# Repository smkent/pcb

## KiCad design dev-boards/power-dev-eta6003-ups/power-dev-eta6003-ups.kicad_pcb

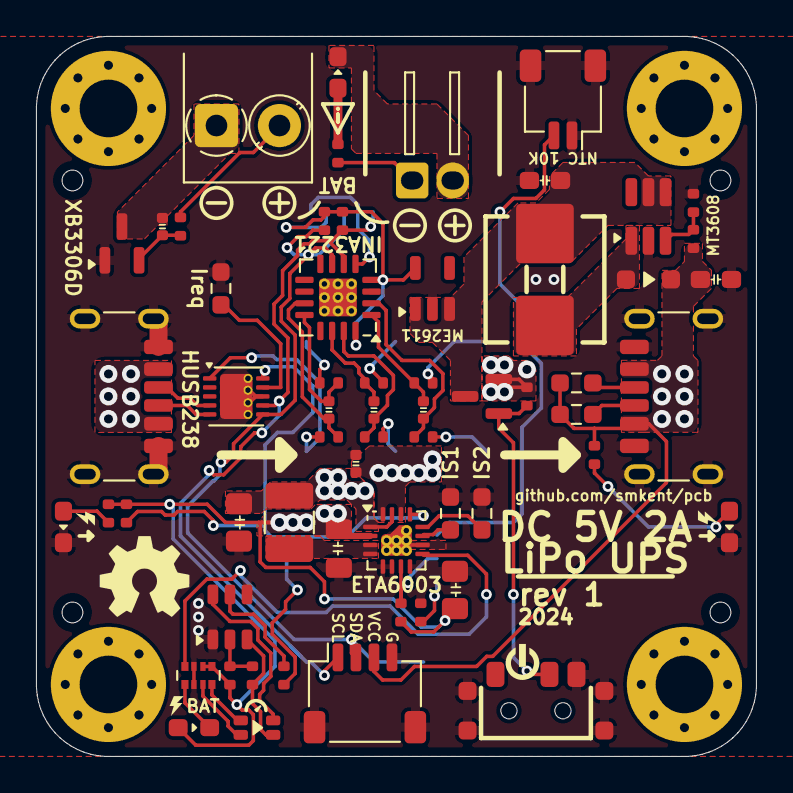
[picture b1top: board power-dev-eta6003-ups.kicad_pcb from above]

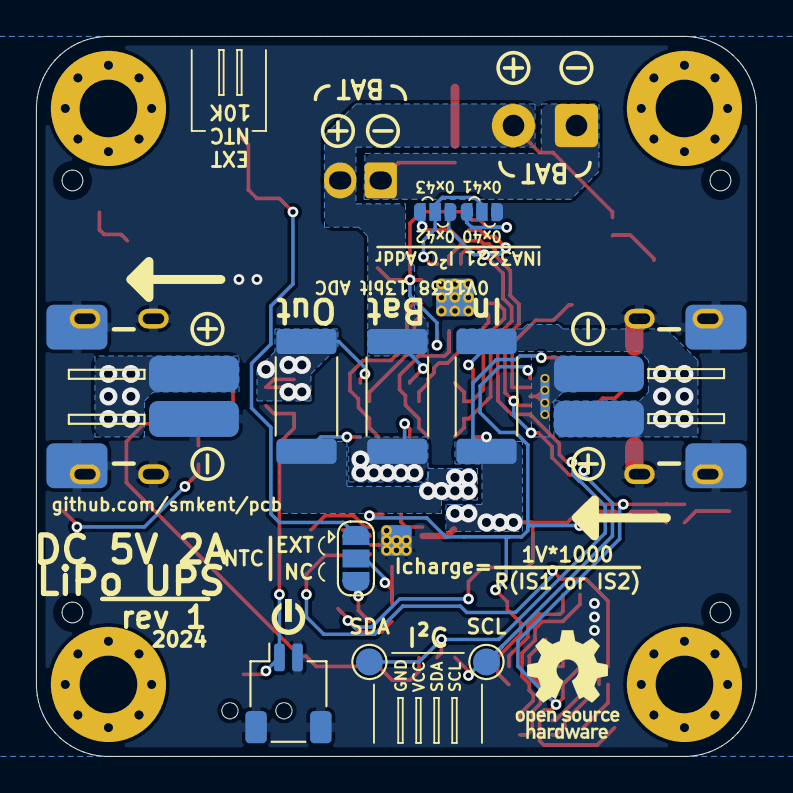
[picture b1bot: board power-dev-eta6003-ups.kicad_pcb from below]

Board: 2 copper layers, 40.0 x 40.0 mm, 71 parts (11 on the bottom side), 47 nets.

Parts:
C1: 22u; C_0805_2012Metric_Pad1.18x1.45mm_HandSolder
C2: 1u; C_0402_1005Metric_simple
C3: 10u; C_0805_2012Metric_Pad1.18x1.45mm_wide-center_HandSolder
C4, C7, C8, C9: 0u1; C_0402_1005Metric_simple
C5, C6: 10u; C_0603_1608Metric_Pad1.08x0.95mm_HandSolder
C10: 10u; C_0805_2012Metric_Pad1.18x1.45mm_HandSolder
D1: BAT60A; D_SOD-323_HandSoldering_simple
J1: P3.5; TerminalBlock_Phoenix_PT-1,5-2-3.5-H_1x02_P3.50mm_Horizonta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
J100, J200: USB_C_Receptacle_PowerOnly_6P; USB_C_Receptacle_GCT_USB4125-xx-x_6P_TopMnt_Horizontal_hand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
J101, J201: JST XH/PH; Conn_Combo_JST-1x02-XH_PH-SMD-alt-pad2gnd
J300: JST XH/PH; Conn_Combo_JST-1x02-XH_PH-THT-pad2gnd
J301, J500: JST SH; JST_SH_SM02B-SRSS-TB_1x02-1MP_P1.00mm_Horizontal
J400: JST SH; JST_SH_SM04B-SRSS-TB_1x04-1MP_P1.00mm_Horizontal
JP1: NTC; SolderJumper-3_P1.3mm_Open_RoundedPad1.0x1.5mm
JP2, JP3: VS/GND; SolderJumper-3_P1.0mm_Open_RoundedPad_simple
L1: 2u2; L_1210_3225Metric_Pad1.42x2.65mm_HandSolder
L2: 4u7; Inductor_Multi_7.0x6.6_1210
LED1: Pink; LED_0603_1608Metric_Pad1.05x0.95mm_HandSolder_simple
LED2: LED; LED-ARRAY-SMD_4P-L2.0-W1.3-RD
LED3: White; LED_0603_1608Metric_Pad1.05x0.95mm_HandSolder_simple
LED4: Red; LED_0603_1608Metric_Pad1.05x0.95mm_HandSolder_simple
LED5: Blue; LED_0603_1608Metric_Pad1.05x0.95mm_HandSolder_simple
Q1: 2N7002DW; SOT-23-6_trimmed-pads_simple
Q2: AO3401A; SOT-23_simple
R1, R2, R8, R9, R10, R13, R25, R104: 10K; R_0402_1005Metric_simple
R3, R11, R103: 5K1; R_0402_1005Metric_simple
R4: 2K; R_0603_1608Metric_Pad0.98x0.95mm_HandSolder
R5: 1K; R_0603_1608Metric_Pad0.98x0.95mm_HandSolder
R6, R7, R27, R28, R29, R30, R31, R32: 10R; R_0402_1005Metric_simple
R12: 100R; R_0402_1005Metric_simple
R24: 75K; R_0402_1005Metric_simple
R102, R201, R202: 22K; R_0603_1608Metric_Pad0.98x0.95mm_HandSolder
RN1: 5K1; R_Array_Convex_4x0402
SR1, SR2, SR3: R040; R_2512_6332Metric_Pad1.40x3.35mm_HandSolder
SW1: SW_SPDT; SW-SMD_3P-P1.50_L2.7-W6.6
TP1, TP2: TestPoint_Pad_D1.5mm
U1: ETA6003; ETA6003_QFN-16-1EP_3x3mm_P0.5mm_EP1.7x1.7mm_ThermalVias
U2: XB3306D; SOT-23_simple
U3: ME6211C33M5; SOT-23-5_simple
U4: INA3221; Texas_RGV0016A_VQFN-16-1EP_4x4mm_P0.65mm_EP2.1x2.1mm_Therma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
U5: MT3608; SOT-23-6_Handsoldering_simple
U101: HUSB238_002DD; WDFN-10-1EP_3x3mm_P0.5mm_EP1.8x2.5mm_ThermalVias_half

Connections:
+3V3: JP2.1 (A), R8.1, R9.1, U3.5 (V_{OUT}), U4.4 (VS), U4.16 (VPU)
B+: J1.1, J300.1, LED4.1 (K), R12.2, R30.2, SR2.1
B-: C4.2, J1.2, J300.2, R11.2, U2.3 (GND)
BAT_SHUNT: C2.1, R29.2, SR2.2, U1.14 (BATT), U1.16 (BATT)
BOOST_SW: D1.2 (A), L2.2, U5.1 (SW)
EXT_POWER_SWITCH: J500.1, Q2.1 (G), R10.2, SW1.2 (B)
FB: R24.2, R25.1, U5.3 (FB)
GND: C1.2, C2.2, C3.1, C5.2, C6.2, C10.1, J100.A12 (GND), J100.B12 (GND), J100.S1 (SHIELD), J101.2, J101.MP (MountPin), J200.A12 (GND), J200.B12 (GND), J200.S1 (SHIELD), J201.2, J201.MP (MountPin), J301.1, J301.MP (MountPin), J400.4, J400.MP (MountPin), J500.2, J500.MP (MountPin), JP2.3 (B), LED3.1 (K), LED5.1 (K), Q1.1 (S), Q1.4 (S), R2.1, R4.2, R5.2, R25.2, R102.2, RN1.2 (R2.1), RN1.7 (R2.2), SW1.3 (C), SW1.MP (MountPin), U1.5 (PGND), U1.6 (ENB), U1.8 (ENPPB), U1.10 (GND), U1.17 (EP), U2.1 (VM), U3.2 (V_{SS}), U4.3 (GND), U5.2 (GND), U101.8 (VSET), U101.11 (GND)
LOAD_SHUNT: C1.1, L1.1, R31.2, SR3.2, U1.1 (SYS), U1.15 (SYS)
LOAD_SHUNT_OUT: Q2.2 (S), R10.1, R32.2, SR3.1
NTC: JP1.2 (C), R1.1, U1.7 (NTC)
NTC_CONN: J301.2, JP1.1 (A)
unnamed: J100.A5 (CC1), U101.4 (CC1)
unnamed: J100.B5 (CC2), U101.5 (CC2)
unnamed: J200.A5 (CC1), R201.2
unnamed: J200.B5 (CC2), R202.2
unnamed: JP1.3 (B), R2.2
unnamed: JP2.2 (C), JP3.2 (C), U4.5 (A0)
unnamed: LED1.1 (K), RN1.1 (R1.1)
unnamed: LED2.1 (RED_A), RN1.3 (R3.1)
unnamed: LED2.2 (RED_K), Q1.3 (D), R7.1
unnamed: LED2.3 (BLUE_A), RN1.4 (R4.1)
unnamed: LED2.4 (BLUE_K), Q1.6 (D)
unnamed: LED3.2 (A), R103.2
unnamed: LED4.2 (A), R11.1
unnamed: LED5.2 (A), R3.2
unnamed: Q1.5 (G), R6.1
unnamed: Q1.2 (G), R7.2, R13.2
unnamed: RN1.8 (R1.2), U1.9 (STAT)
unnamed: R4.1, U1.11 (ISET1)
unnamed: R5.1, U1.12 (ISET2)
unnamed: C4.1, R12.1, U2.2 (VDD)
unnamed: C7.1, R27.2, U4.12 (IN+1)
unnamed: C8.1, R29.1, U4.15 (IN+2)
unnamed: C9.1, R31.1, U4.2 (IN+3)
unnamed: C7.2, R28.2, U4.11 (IN-1)
unnamed: C8.2, R30.1, U4.14 (IN-2)
unnamed: C9.2, R32.1, U4.1 (IN-3)
unnamed: R102.1, U101.9 (ISET)
SCL: J400.1, JP3.1 (A), R9.2, TP1.1, U4.6 (SCL), U101.7 (SCL)
SDA: J400.2, JP3.3 (B), R8.2, TP2.1, U4.7 (SDA), U101.6 (SDA)
SW: L1.2, U1.3 (SW), U1.4 (SW)
USB_DET: R6.2, R104.2, U1.13 (USB_DET), U101.10 (GATE)
VIN: J100.A9 (VBUS), J100.B9 (VBUS), J101.1, R27.1, SR1.1
VIN_SHUNT: C3.2, C10.2, LED1.2 (A), R1.2, R13.1, R28.1, R103.1, R104.1, RN1.5 (R4.2), RN1.6 (R3.2), SR1.2, U1.2 (IN), U101.1 (VIN)
VOUT: C6.1, D1.1 (K), J200.A9 (VBUS), J200.B9 (VBUS), J201.1, J400.3, R3.1, R24.1, R201.1, R202.1
VSYS: C5.1, L2.1, Q2.3 (D), U3.1 (V_{IN}), U3.3 (CE), U5.4 (EN), U5.5 (IN)

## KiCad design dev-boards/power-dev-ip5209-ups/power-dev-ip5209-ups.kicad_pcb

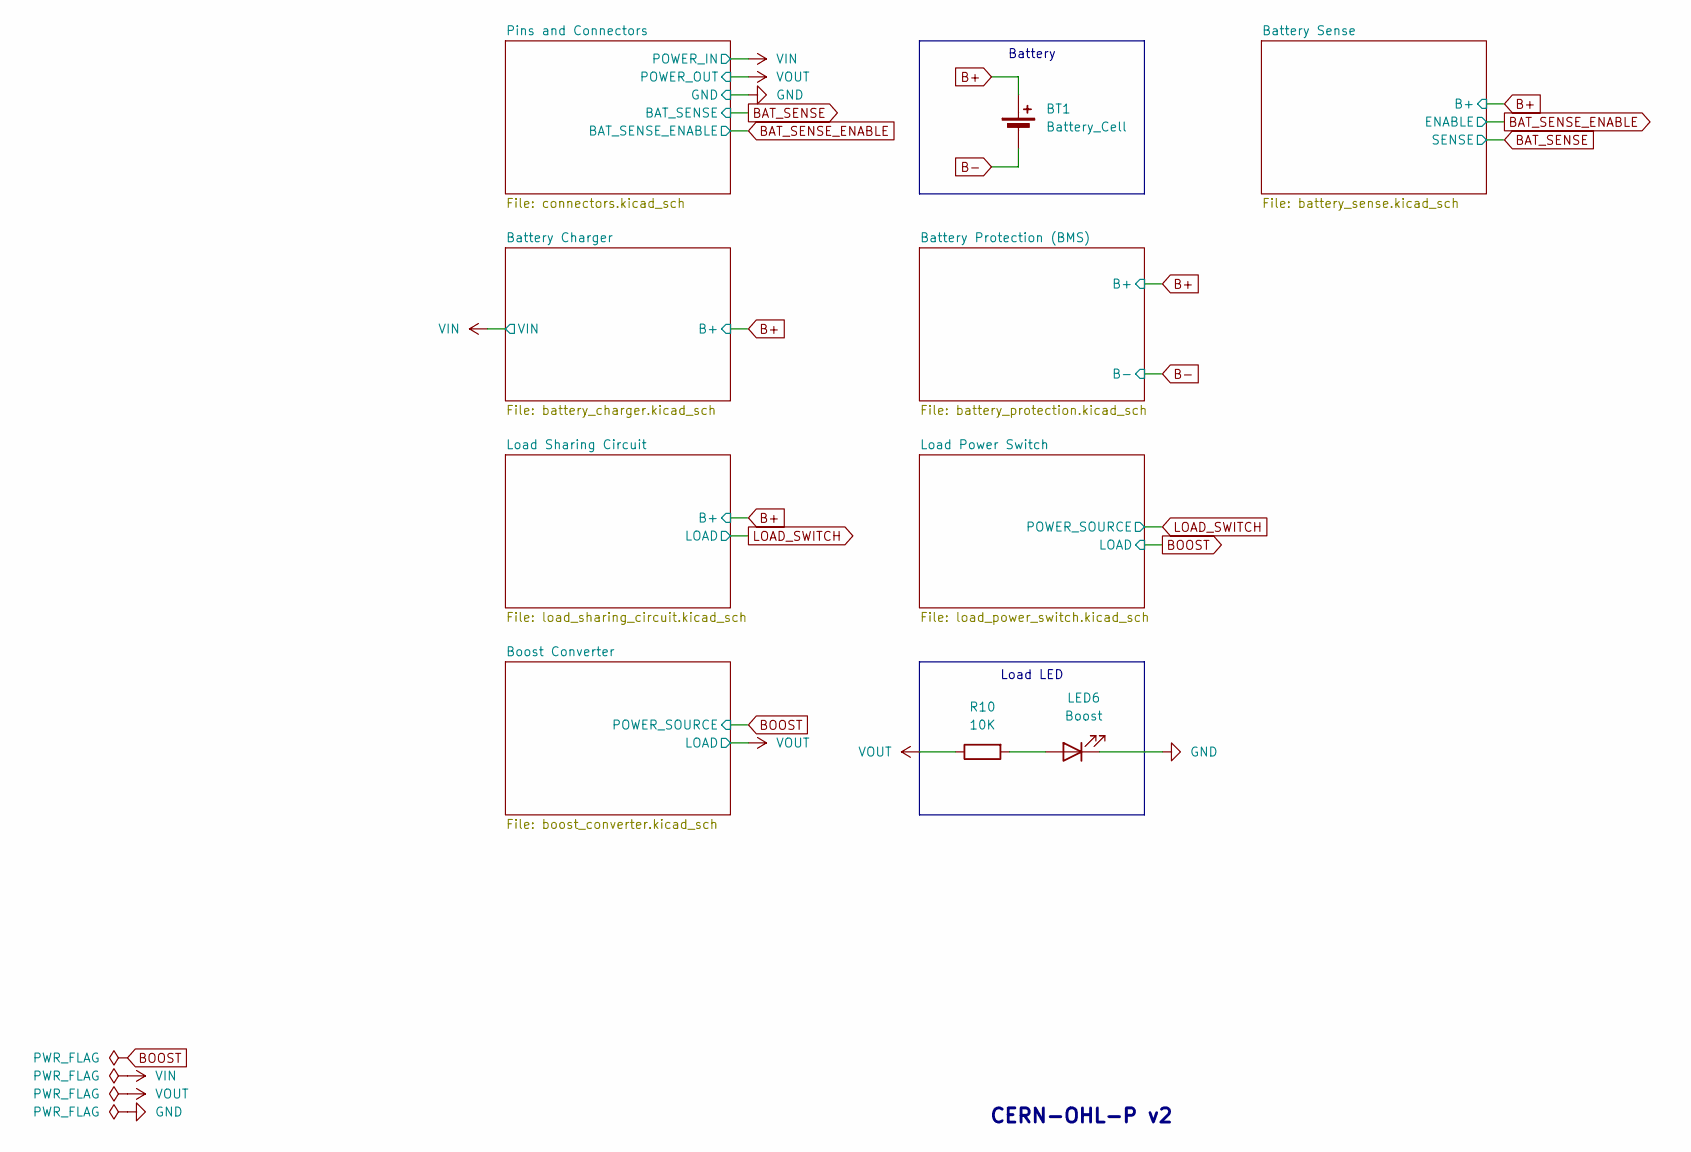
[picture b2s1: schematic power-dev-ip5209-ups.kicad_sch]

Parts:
BT1: Battery_Cell; JST_XH_S2B-XH-2AW_1x02_P2.50mm_pad2gnd_trim
LED6: Boost; LED_0805_2012Metric_Pad1.15x1.40mm_HandSolder_simple
R10: 10K; R_0402_1005Metric; LCSC Part C25744

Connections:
B+: BT1.1 (+); also elsewhere on the board
B-: BT1.2 (-); also elsewhere on the board
GND: LED6.1 (K); also elsewhere on the board
unnamed: LED6.2 (A), R10.2
VOUT: R10.1; also elsewhere on the board

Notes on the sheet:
Battery
Load LED
CERN-OHL-P v2

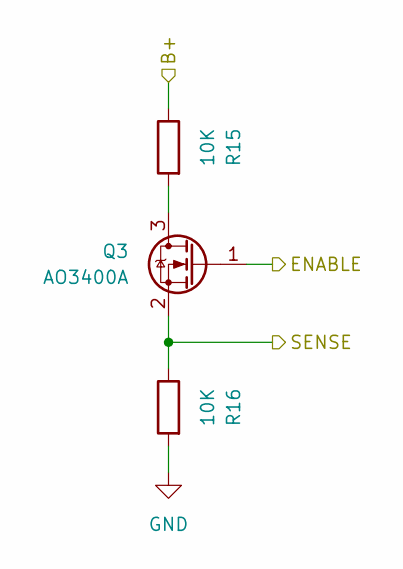
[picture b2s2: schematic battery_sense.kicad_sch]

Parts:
Q3: AO3400A; SOT-23
R15, R16: 10K; R_0402_1005Metric; LCSC Part C25744

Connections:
B+: R15.1; also elsewhere on the board
BAT_SENSE: Q3.2 (S), R16.1; also elsewhere on the board
BAT_SENSE_ENABLE: Q3.1 (G); also elsewhere on the board
GND: R16.2; also elsewhere on the board
unnamed: Q3.3 (D), R15.2

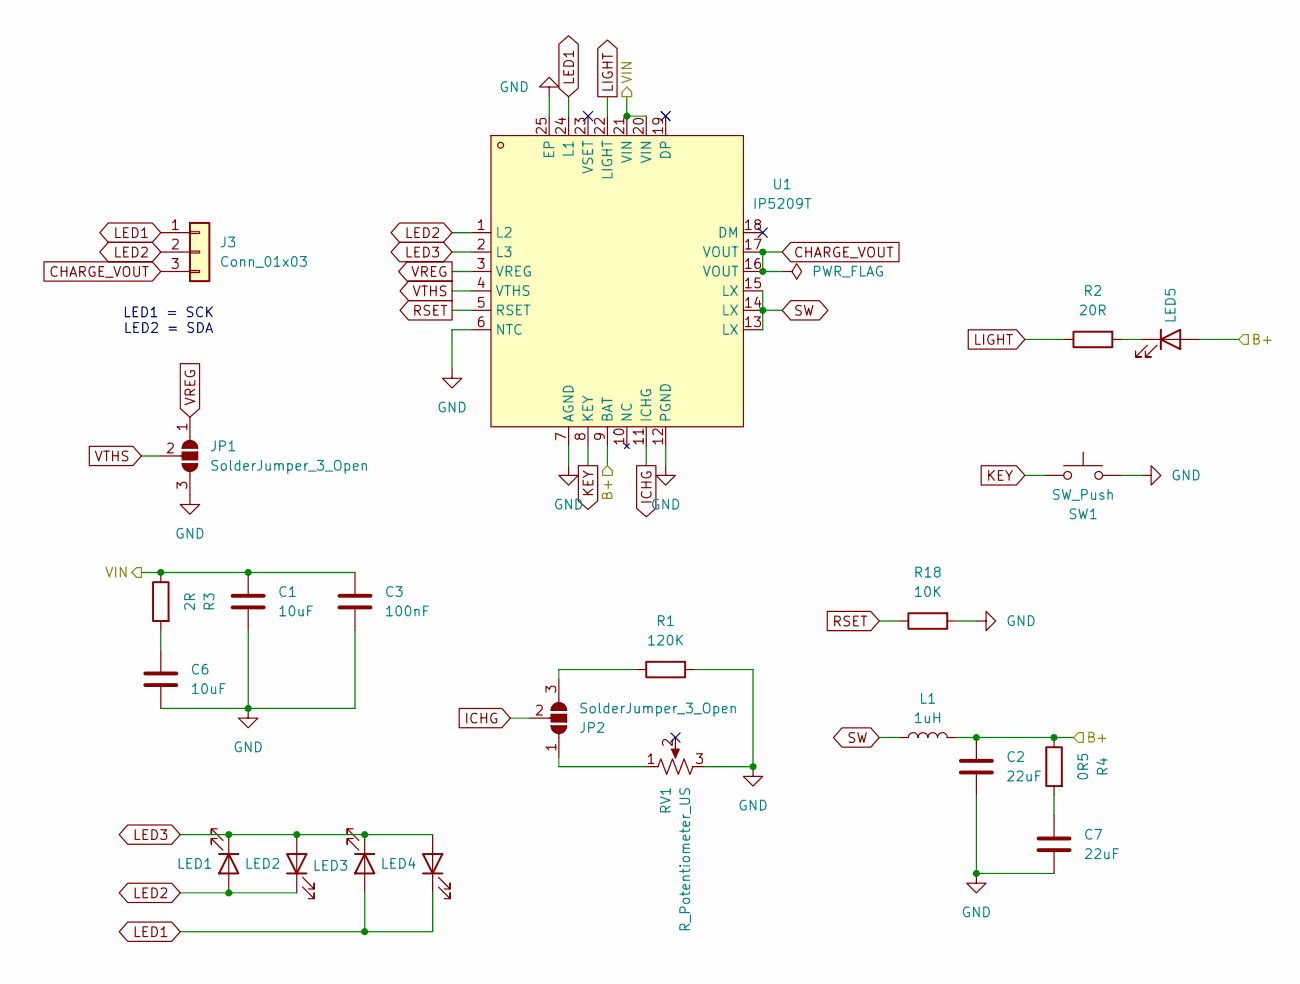
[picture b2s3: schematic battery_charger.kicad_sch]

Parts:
C1, C6: 10uF; C_0402_1005Metric; LCSC Part C15525
C2, C7: 22uF; C_0603_1608Metric; LCSC Part C59461
C3: 100nF; C_0402_1005Metric; LCSC Part C307331
J3: Conn_01x03; PinHeader_1x03_P2.54mm_Vertical_simple
JP1, JP2: SolderJumper_3_Open; SolderJumper-3_P1.3mm_Open_RoundedPad1.0x1.5mm
L1: 1uH; L_1210_3225Metric; LCSC Part C3002559
LED1, LED2, LED3, LED4: LED_0805_2012Metric_Pad1.15x1.40mm_HandSolder_simple
LED5: LED-SMD_3P-L5.7-W3.0-RD
R1: 120K; R_0805_2012Metric_Pad1.20x1.40mm_HandSolder; LCSC Part C17436
R2: 20R; R_0805_2012Metric_Pad1.20x1.40mm_HandSolder; LCSC Part C17544
R3: 2R; R_0603_1608Metric; LCSC Part C22977
R4: 0R5; R_0805_2012Metric_Pad1.20x1.40mm_HandSolder
R18: 10K; R_0805_2012Metric_Pad1.20x1.40mm_HandSolder
RV1: R_Potentiometer_US; RES-ADJ-SMD_VG039NCH
SW1: SW_Push; SW-SMD_BZCN_TSA002A35XXX
U1: IP5209T; QFN-24-1EP_4x4mm_P0.5mm_EP2.6x2.6mm_ThermalVias; LCSC Part C284964

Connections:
B+: C2.1, L1.2, LED5.2 (A), R4.1, U1.9 (BAT); also elsewhere on the board
CHARGE_VOUT: J3.3, U1.16 (VOUT), U1.17 (VOUT)
GND: C1.2, C2.2, C3.2, C6.2, C7.2, JP1.3 (B), R1.2, R18.2, RV1.3, SW1.1, U1.6 (NTC), U1.7 (AGND), U1.12 (PGND), U1.25 (EP); also elsewhere on the board
ICHG: JP2.2 (C), U1.11 (ICHG)
KEY: SW1.2, U1.8 (KEY)
LED1: J3.1, LED3.2 (A), LED4.1 (K), U1.24 (L1)
LED2: J3.2, LED1.2 (A), LED2.1 (K), U1.1 (L2)
LED3: LED1.1 (K), LED2.2 (A), LED3.1 (K), LED4.2 (A), U1.2 (L3)
LIGHT: R2.1, U1.22 (LIGHT)
unnamed: C6.1, R3.2
unnamed: C7.1, R4.2
unnamed: JP2.1 (A), RV1.1
unnamed: JP2.3 (B), R1.1
unnamed: LED5.1 (K), R2.2
RSET: R18.1, U1.5 (RSET)
SW: L1.1, U1.13 (LX), U1.14 (LX), U1.15 (LX)
VIN: C1.1, C3.1, R3.1, U1.20 (VIN), U1.21 (VIN); also elsewhere on the board
VREG: JP1.1 (A), U1.3 (VREG)
VTHS: JP1.2 (C), U1.4 (VTHS)

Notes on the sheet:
LED1 = SCK LED2 = SDA

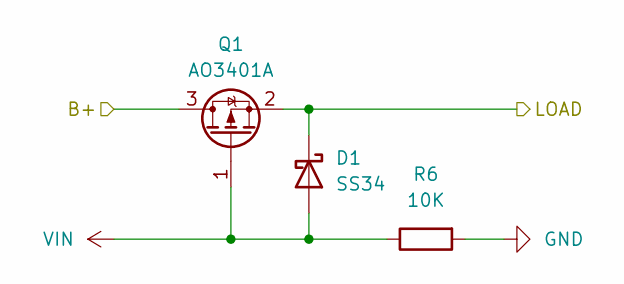
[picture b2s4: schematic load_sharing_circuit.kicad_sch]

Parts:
D1: SS34; D_SMA_simple; LCSC Part C8678
Q1: AO3401A; SOT-23; LCSC Part C15127
R6: 10K; R_0402_1005Metric; LCSC Part C25744

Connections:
B+: Q1.3 (D); also elsewhere on the board
GND: R6.2; also elsewhere on the board
LOAD_SWITCH: D1.1 (K), Q1.2 (S); also elsewhere on the board
VIN: D1.2 (A), Q1.1 (G), R6.1; also elsewhere on the board

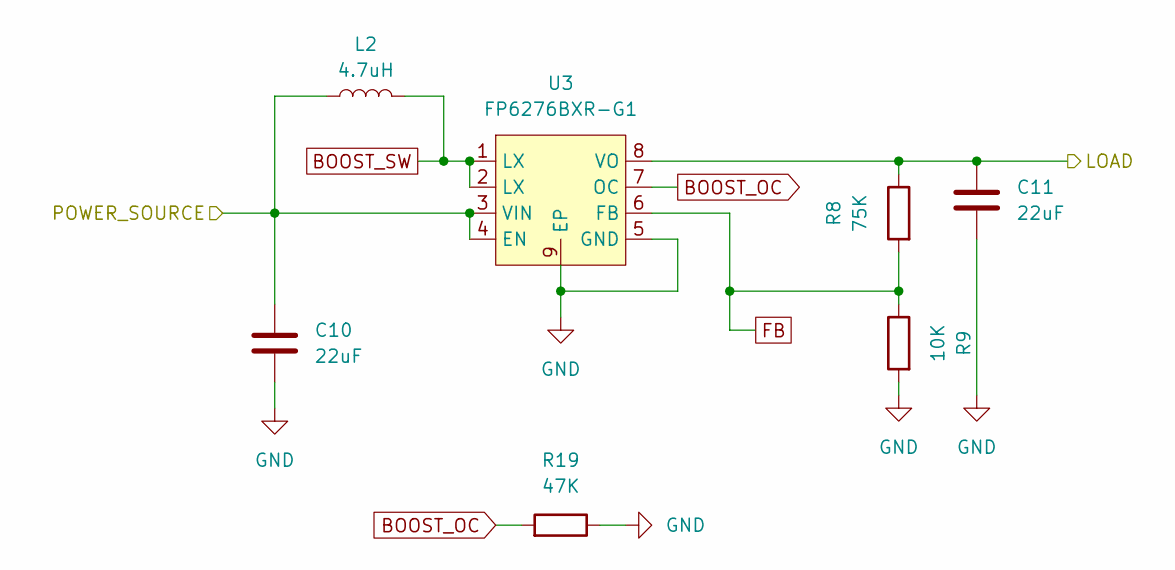
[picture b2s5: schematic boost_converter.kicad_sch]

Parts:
C10, C11: 22uF; C_0603_1608Metric; LCSC Part C59461
L2: 4.7uH; IND-SMD_L7.0-W6.6; LCSC Part C5307631
R8: 75K; R_0402_1005Metric; LCSC Part C25798
R9: 10K; R_0402_1005Metric; LCSC Part C25744
R19: 47K; R_0805_2012Metric_Pad1.20x1.40mm_HandSolder; LCSC Part C17713
U3: FP6276BXR-G1; SOIC-8-1EP_3.9x4.9mm_P1.27mm_EP2.41x3.3mm_ThermalVias_Custo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; LCSC Part C82652

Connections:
BOOST: C10.1, L2.1, U3.3 (VIN), U3.4 (EN); also elsewhere on the board
BOOST_OC: R19.2, U3.7 (OC)
BOOST_SW: L2.2, U3.1 (LX), U3.2 (LX)
FB: R8.2, R9.1, U3.6 (FB)
GND: C10.2, C11.2, R9.2, R19.1, U3.5 (GND), U3.9 (EP); also elsewhere on the board
VOUT: C11.1, R8.1, U3.8 (VO); also elsewhere on the board

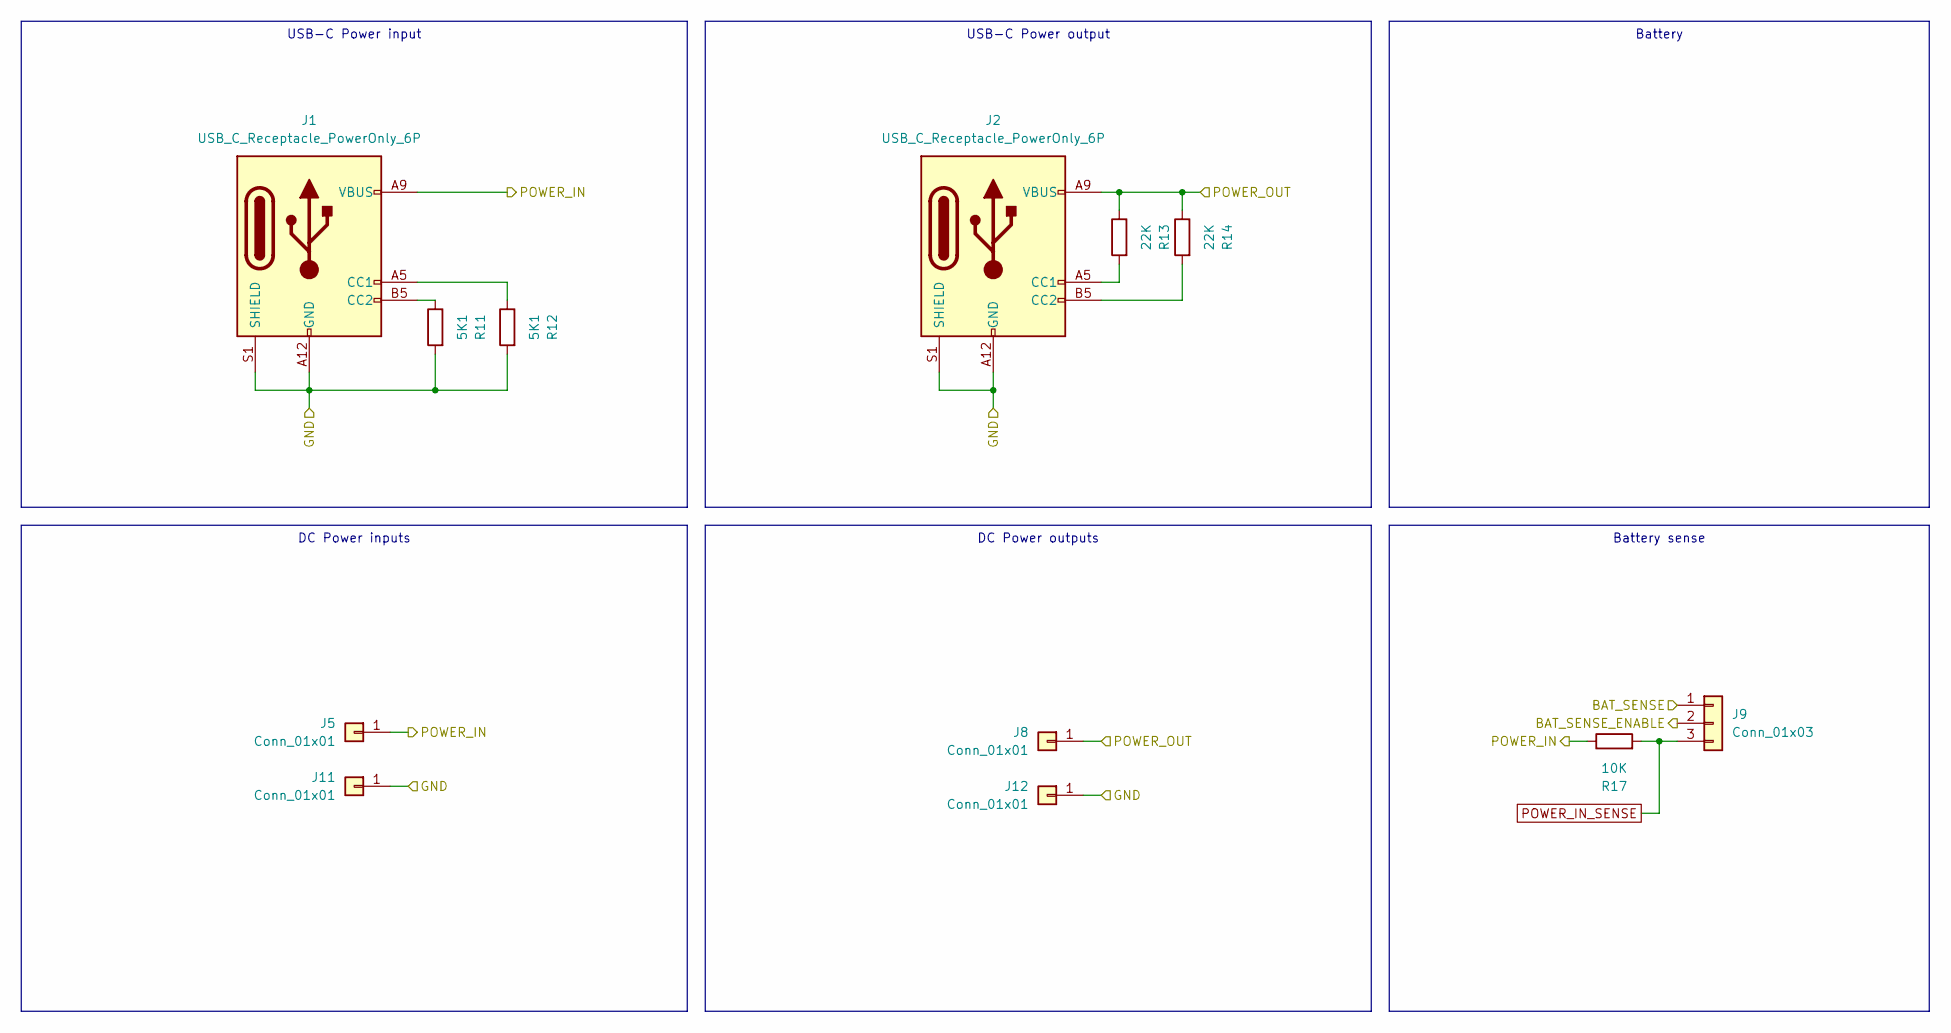
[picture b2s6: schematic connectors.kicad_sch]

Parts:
J1, J2: USB_C_Receptacle_PowerOnly_6P; USB_C_Receptacle_GCT_USB4125-xx-x_6P_TopMnt_Horizontal_hand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
J5, J8: Conn_01x01; PinHeader_1x01_P2.54mm_simple
J9: Conn_01x03; PinHeader_1x03_P2.54mm_Vertical_simple
J11, J12: Conn_01x01; PinHeader_1x01_P2.54mm_simple_square
R11, R12: 5K1; R_0402_1005Metric; LCSC Part C25905
R13, R14: 22K; R_0402_1005Metric; LCSC Part C25768
R17: 10K; R_0402_1005Metric; LCSC Part C25744

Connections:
BAT_SENSE: J9.1; also elsewhere on the board
BAT_SENSE_ENABLE: J9.2; also elsewhere on the board
GND: J1.A12 (GND), J1.B12 (GND), J1.S1 (SHIELD), J2.A12 (GND), J2.B12 (GND), J2.S1 (SHIELD), J11.1, J12.1, R11.2, R12.2; also elsewhere on the board
unnamed: J1.A5 (CC1), R12.1
unnamed: J1.B5 (CC2), R11.1
unnamed: J2.A5 (CC1), R13.2
unnamed: J2.B5 (CC2), R14.2
POWER_IN_SENSE: J9.3, R17.2
VIN: J1.A9 (VBUS), J1.B9 (VBUS), J5.1, R17.1; also elsewhere on the board
VOUT: J2.A9 (VBUS), J2.B9 (VBUS), J8.1, R13.1, R14.1; also elsewhere on the board

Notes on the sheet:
DC Power outputs
USB-C Power output
DC Power inputs
Battery sense
USB-C Power input
Battery

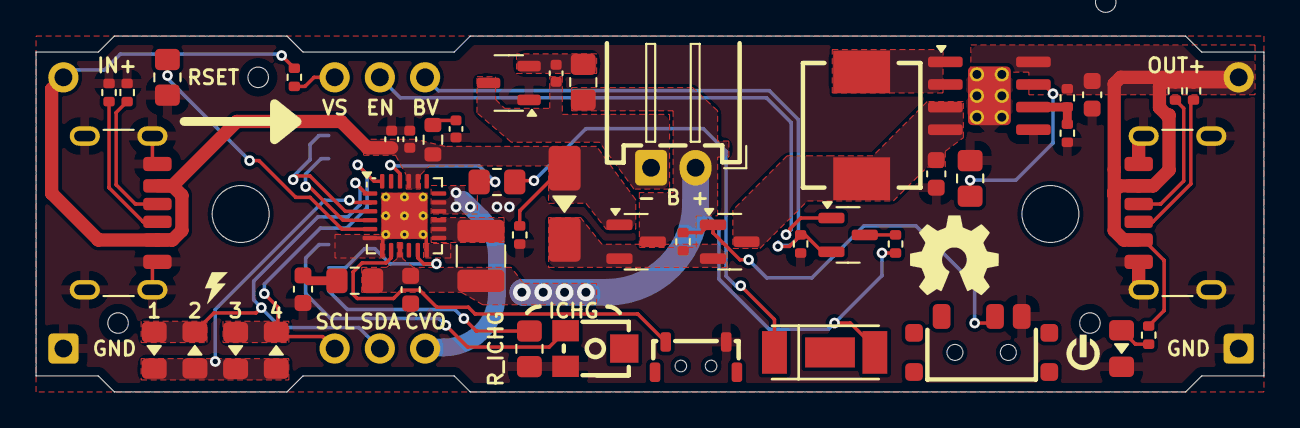
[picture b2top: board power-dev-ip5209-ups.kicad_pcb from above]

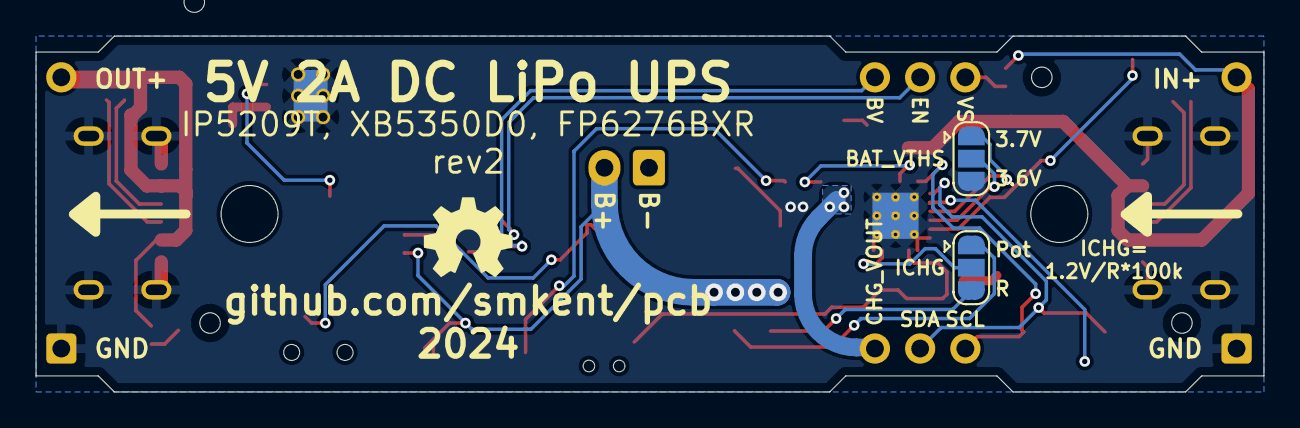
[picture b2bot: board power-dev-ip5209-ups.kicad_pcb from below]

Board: 2 copper layers, 69.0 x 20.0 mm, 56 parts (8 on the bottom side), 37 nets.

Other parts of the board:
C9: 0.1uF; C_0402_1005Metric
Q2: AO3401A; SOT-23
R5: 100R; R_0805_2012Metric_Pad1.20x1.40mm_HandSolder
R7: 10K; R_0402_1005Metric
SW2: SW_SPDT; SW-SMD_3P-P1.50_L2.7-W6.6
U2: XB3306D; SOT-23-3

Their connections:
B+: R5.1; also elsewhere on the board
B-: C9.1, U2.3 (GND); also elsewhere on the board
BATVDD: C9.2, R5.2, U2.2 (VDD)
BOOST: Q2.3 (D); also elsewhere on the board
GND: SW2.3 (C), U2.1 (VM); also elsewhere on the board
LOAD_SWITCH: Q2.2 (S), R7.1; also elsewhere on the board
unnamed: Q2.1 (G), R7.2, SW2.2 (B)

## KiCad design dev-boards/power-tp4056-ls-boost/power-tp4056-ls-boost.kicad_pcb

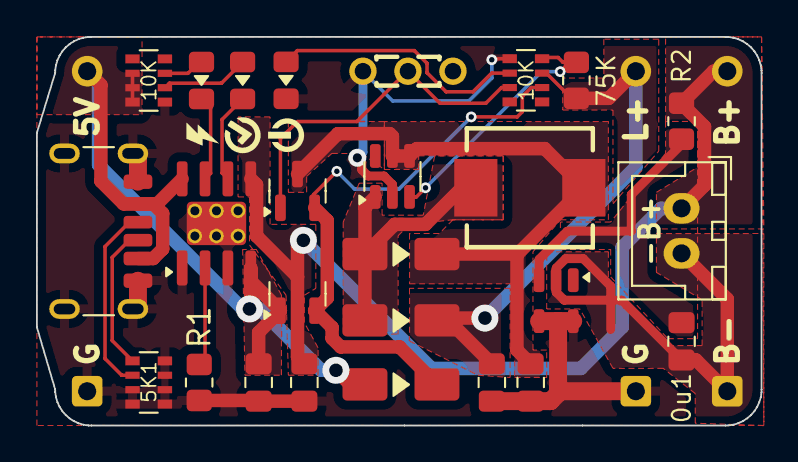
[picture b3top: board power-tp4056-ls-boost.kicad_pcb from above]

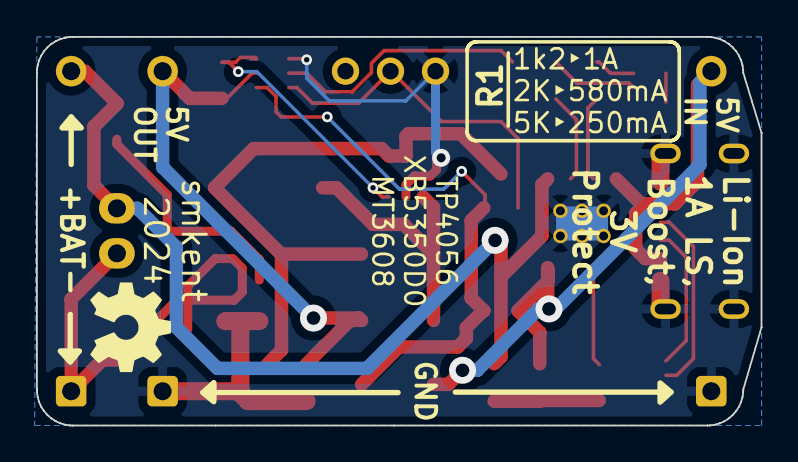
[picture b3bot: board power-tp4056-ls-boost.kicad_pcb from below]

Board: 2 copper layers, 40.3 x 21.6 mm, 32 parts (6 on the bottom side), 19 nets.

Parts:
BT1: Battery_Cell; JST_XH_B2B-XH-A_1x02_P2.50mm_Vertical_simple
C1, C2, C4, C5: 10uF; C_0805_2012Metric_Pad1.18x1.45mm_HandSolder
C3: 0.1uF; C_0805_2012Metric_Pad1.18x1.45mm_HandSolder
D1, D2, D3: SS34; D_SMA_simple
J0: USB_C_Receptacle_PowerOnly_6P; USB_C_Receptacle_GCT_USB4125-xx-x_6P_TopMnt_Horizontal_hand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
J1, J3, J5: Conn_01x01; PinHeader_1x01_P2.54mm_simple
J2, J4, J6: Conn_01x01; PinHeader_1x01_P2.54mm_simple_square
L1: 22uH; IND-SMD_L7.0-W6.6
LED1: Charge; LED_0805_2012Metric_Pad1.15x1.40mm_HandSolder_simple
LED2: Done; LED_0805_2012Metric_Pad1.15x1.40mm_HandSolder_simple
LED3: Boost; LED_0805_2012Metric_Pad1.15x1.40mm_HandSolder_simple
Q1, Q2: AO3401A; SOT-23
R1: 1K2; R_0805_2012Metric_Pad1.20x1.40mm_HandSolder
R2: 100R; R_0805_2012Metric_Pad1.20x1.40mm_HandSolder
R3: 75K; R_0805_2012Metric_Pad1.20x1.40mm_HandSolder
RN1, RN3: 10K; R_Array_Convex_4x0603
RN2: 5K1; R_Array_Convex_4x0603
SW1: SW_SPDT; SW-TH_DEALON_SS-12D01-GX_simple
U1: TP4056; SOIC-8-1EP_3.9x4.9mm_P1.27mm_EP2.41x3.3mm_ThermalVias_Custo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
U2: XB5350D0; SOT-23-5_simple
U3: MT3608; SOT-23-6

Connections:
B+: BT1.1 (+), C2.2, J3.1, Q1.3 (D), R2.1, U1.5 (BAT)
B-: BT1.2 (-), C3.1, J4.1, U2.2 (GND)
BATVDD: C3.2, R2.2, U2.3 (VDD)
BOOST: C4.1, D3.1 (K), L1.1, Q2.3 (D), U3.4 (EN), U3.5 (IN)
GND: C1.2, C2.1, C4.2, C5.2, J0.A12 (GND), J0.B12 (GND), J0.S1 (SHIELD), J2.1, J6.1, LED3.1 (K), R1.2, RN1.1 (R1.1), RN2.3 (R3.1), RN2.4 (R4.1), RN2.5 (R4.2), RN2.6 (R3.2), RN2.7 (R2.2), RN2.8 (R1.2), RN3.5 (R4.2), SW1.3 (C), U1.1 (TEMP), U1.3 (GND), U1.9 (EP), U2.4 (VM), U2.5 (VM), U3.2 (GND)
LOAD_SWITCH: D1.1 (K), Q1.2 (S), Q2.2 (S), RN3.2 (R2.1)
unnamed: D2.2 (A), D3.2 (A), L1.2, U3.1 (SW)
unnamed: J0.A5 (CC1), RN2.2 (R2.1)
unnamed: J0.B5 (CC2), RN2.1 (R1.1)
unnamed: LED1.2 (A), RN1.3 (R3.1)
unnamed: LED1.1 (K), U1.7 (~CHRG)
unnamed: LED2.2 (A), RN1.2 (R2.1)
unnamed: LED2.1 (K), U1.6 (~STDBY)
unnamed: LED3.2 (A), RN3.6 (R3.2)
unnamed: Q2.1 (G), RN3.7 (R2.2), SW1.2 (B)
unnamed: R3.2, RN3.4 (R4.1), U3.3 (FB)
unnamed: R1.1, U1.2 (PROG)
VIN: C1.1, D1.2 (A), J0.A9 (VBUS), J0.B9 (VBUS), J1.1, Q1.1 (G), RN1.6 (R3.2), RN1.7 (R2.2), RN1.8 (R1.2), U1.4 (VCC), U1.8 (CE)
VOUT: C5.1, D2.1 (K), J5.1, R3.1, RN3.3 (R3.1)

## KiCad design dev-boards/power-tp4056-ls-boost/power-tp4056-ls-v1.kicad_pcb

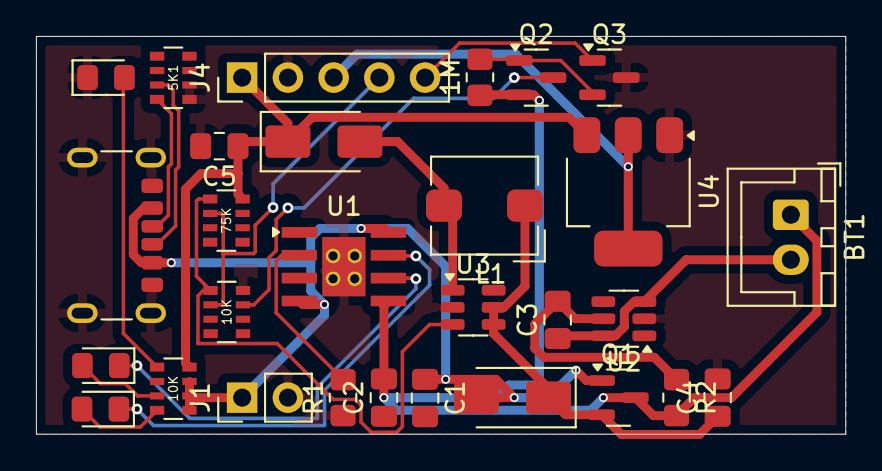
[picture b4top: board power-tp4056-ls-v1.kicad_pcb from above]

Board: 2 copper layers, 45.0 x 22.1 mm, 29 parts (0 on the bottom side), 22 nets.

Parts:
BT1: Battery_Cell; JST_XH_B2B-XH-A_1x02_P2.50mm_Vertical
C1, C2, C4, C5: 10uF; C_0805_2012Metric_Pad1.18x1.45mm_HandSolder
C3: 0.1uF; C_0805_2012Metric_Pad1.18x1.45mm_HandSolder
D1, D3: SS34; D_SMA
J1: Conn_01x02; PinHeader_1x02_P2.54mm_Vertical
J4: Conn_01x05; PinHeader_1x05_P2.54mm_Vertical
J5: USB_C_Receptacle_PowerOnly_6P; USB_C_Receptacle_GCT_USB4125-xx-x_6P_TopMnt_Horizontal
L1: 22uH; L_Bourns_SRP5030T
LED1: Charge; LED_0805_2012Metric_Pad1.15x1.40mm_HandSolder
LED2: Done; LED_0805_2012Metric_Pad1.15x1.40mm_HandSolder
LED3: Boost; LED_0805_2012Metric_Pad1.15x1.40mm_HandSolder
Q1, Q2: AO3401A; SOT-23
Q3: BSS138; SOT-23
R1: 1K2; R_0805_2012Metric_Pad1.20x1.40mm_HandSolder
R2: 100R; R_0805_2012Metric_Pad1.20x1.40mm_HandSolder
R5: 1M; R_0805_2012Metric_Pad1.20x1.40mm_HandSolder
RN1, RN3: 10K; R_Array_Convex_4x0603
RN2: 5K1; R_Array_Convex_4x0603
RN4: 75K; R_Array_Convex_4x0603
U1: TP4056; TP4056-SOP-8-EP-Vias
U2: XB5307H; SOT-23-6
U3: MT3608; SOT-23-6
U4: AMS1117-3.3; SOT-223-3_TabPin2

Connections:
+3V3: J4.3, U4.2 (VO)
B+: BT1.1 (+), C2.2, Q1.3 (D), Q2.2 (S), R2.2, R5.2, U1.5 (BAT)
B-: BT1.2 (-), C3.1, U2.3 (GND), U2.6 (GND)
BAT_SENSE: J4.4, RN3.2 (R2.1), RN4.2 (R2.1)
BAT_SENSE_SWITCH: J4.5, Q3.1 (G)
BOOST: C4.1, D3.1 (K), L1.1, Q1.2 (S), U3.4 (EN), U3.5 (IN)
GND: C1.2, C2.1, C4.2, C5.2, J1.2, J4.2, J5.A12 (GND), J5.B12 (GND), J5.S1 (SHIELD), LED3.1 (K), Q3.3 (D), R1.1, RN1.6 (R3.2), RN2.1 (R1.1), RN2.2 (R2.1), RN3.8 (R1.2), RN4.7 (R2.2), U1.1 (TEMP), U1.3 (GND), U1.9 (EP), U2.2 (VM), U3.2 (GND), U4.1 (GND)
unnamed: D1.2 (A), L1.2, U3.1 (SW)
unnamed: J5.A5 (CC1), RN2.8 (R1.2)
unnamed: J5.B5 (CC2), RN2.7 (R2.2)
unnamed: LED1.2 (A), RN1.8 (R1.2)
unnamed: LED1.1 (K), U1.7 (CHRG)
unnamed: LED2.2 (A), RN1.7 (R2.2)
unnamed: LED2.1 (K), U1.6 (STDBY)
unnamed: LED3.2 (A), RN1.5 (R4.2)
unnamed: Q2.3 (D), RN3.7 (R2.2)
unnamed: Q2.1 (G), Q3.2 (S), R5.1
unnamed: RN3.1 (R1.1), RN4.1 (R1.1), U3.3 (FB)
unnamed: R1.2, U1.2 (PROG)
unnamed: C3.2, R2.1, U2.5 (VDD)
VIN: C1.1, D3.2 (A), J1.1, J5.A9 (VBUS), J5.B9 (VBUS), Q1.1 (G), RN1.1 (R1.1), RN1.2 (R2.1), RN1.3 (R3.1), U1.4 (VCC), U1.8 (CE)
VOUT: C5.1, D1.1 (K), J4.1, RN1.4 (R4.1), RN4.8 (R1.2), U4.3 (VI)

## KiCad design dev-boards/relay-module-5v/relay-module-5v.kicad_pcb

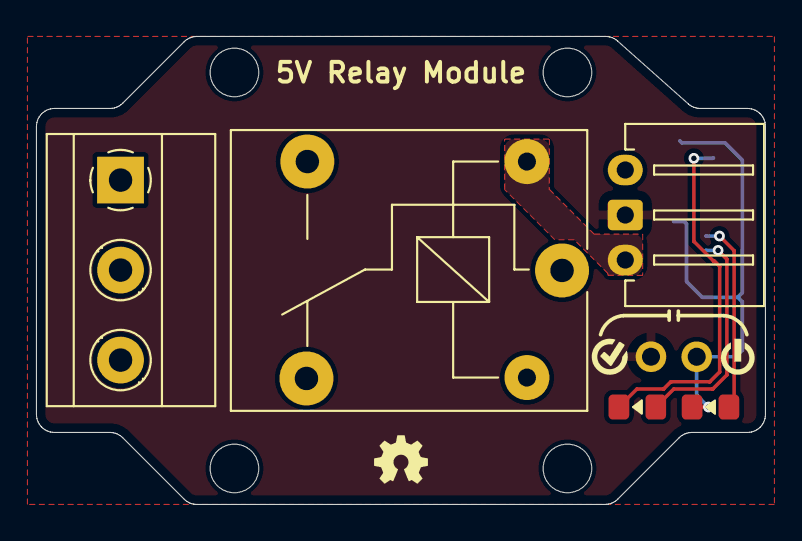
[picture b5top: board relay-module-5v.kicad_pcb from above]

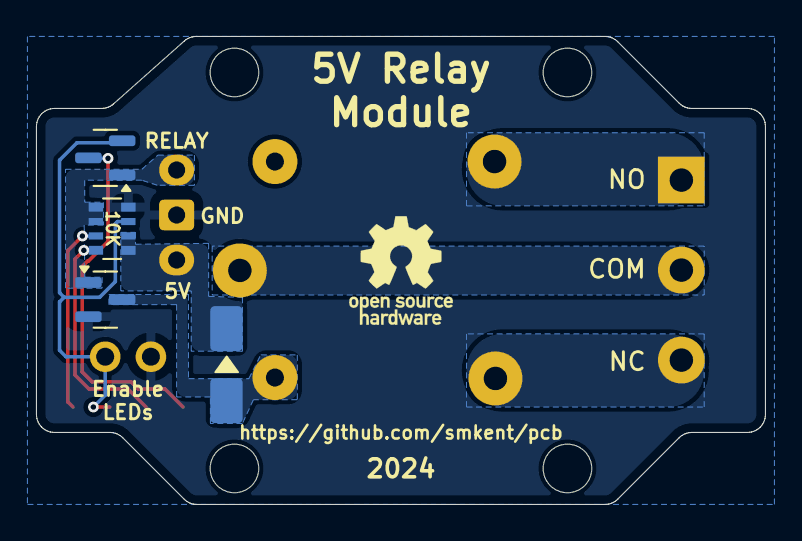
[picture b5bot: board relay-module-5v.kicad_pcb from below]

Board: 2 copper layers, 40.5 x 26.0 mm, 10 parts (4 on the bottom side), 11 nets.

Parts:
D1: SS34; D_SMA_simple
J1: Conn_01x03; JST_XH_S3B-XH_1x03_P2.50mm_Horizontal_pad2gnd
J2: Screw_Terminal_01x03; TerminalBlock_Phoenix_MKDS-1,5-3_1x03_P5.00mm_Horizontal_si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
J3: Conn_01x02; PinHeader_1x02_P2.54mm_Vertical_simple
K1: Relay_SPDT; Relay_SPDT_SANYOU_SRD_Series_Form_C
LED1, LED2: LED; LED_0805_2012Metric_Pad1.15x1.40mm_HandSolder_simple
Q1, Q2: BSS138; SOT-23
RN1: 10K; R_Array_Convex_4x0603

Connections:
+5V: D1.1 (K), J1.1, K1.2, RN1.5 (R4.2), RN1.6 (R3.2)
GND: J1.2, J3.2, Q1.2 (S), RN1.8 (R1.2)
LED_GND: J3.1, LED1.1 (K), Q2.2 (S), RN1.7 (R2.2)
unnamed: LED1.2 (A), RN1.3 (R3.1)
unnamed: LED2.2 (A), RN1.4 (R4.1)
unnamed: LED2.1 (K), Q2.3 (D)
RELAY_COIL: D1.2 (A), K1.5, Q1.3 (D)
RELAY_CONTROL: J1.3, Q1.1 (G), Q2.1 (G), RN1.1 (R1.1), RN1.2 (R2.1)
RELAY_SW_COMMON: J2.2, K1.1
RELAY_SW_NC: J2.3, K1.4
RELAY_SW_NO: J2.1, K1.3
